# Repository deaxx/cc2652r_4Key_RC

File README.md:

# cc2652r/rb/p_4Key_RC
Box
https://aliexpress.ru/item/1005004141598897.html

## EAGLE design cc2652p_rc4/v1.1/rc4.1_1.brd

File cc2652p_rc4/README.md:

# Not recommended for assembly!

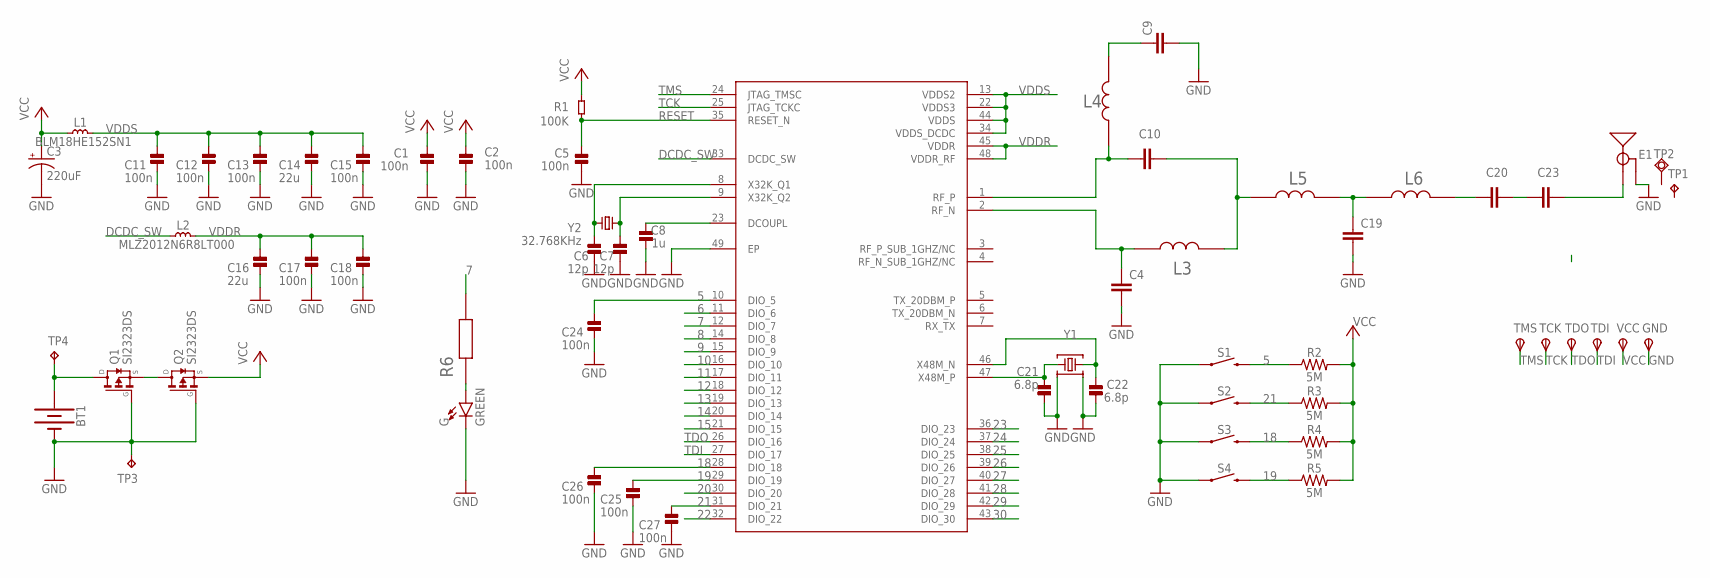
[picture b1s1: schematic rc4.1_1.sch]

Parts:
BT1: BATTERY-20MM_SMD_4LEGS_OVERPASTE; BATTCON_20MM_4LEGS_OVERPASTE
C1, C2, C5, C11, C12, C13, C15, C17, C18, C24, C25, C26, C27: 100n; _PKG_C_0402
C3: 220uF; EIA3528
C4: 1pf; CAPC1005X40N
C6, C7: 12p; _PKG_C_0402
C8: 1u; _PKG_C_0402
C9: 12pF; CAPC1005X40N
C10, C19: 1pF; CAPC1005X40N
C14, C16: 22u; _PKG_C_0805
C20: 12p; CAPC1005X40N
C21, C22: 6.8p; _PKG_C_0402
C23: 1.8pF; CAPC1005X40N
E1: ANTENNA-GROUNDEDTRACE-15.2MM; TRACE_ANTENNA_2.4GHZ_15.2MM
G: GREEN; LED-0603
GND: TPSTP11R; TP11R
IC3: CC2652R1FRGZ; RGZ0048A-IPC_B
L1: BLM18HE152SN1; _PKG_L_0603
L2: MLZ2012N6R8LT000; _PKG_C_0805
L3, L4: 2.4nH; INDC1005X40N
L5, L6: 2nH; INDC1005X40N
Q1, Q2: SI2323DS; SOT23
R1: 100K; _PKG_C_0402
R2, R3, R4, R5: 5M; 0603
R6: 2.2k; RESC1005X40N
S1, S2, S3, S4: MOMENTARY-SWITCH-SPST-SMD-5.2MM; TACTILE_SWITCH_SMD_5.2MM
TCK: TPSTP11R; TP11R
TDI: TPSTP11R; TP11R
TDO: TPSTP11R; TP11R
TMS: TPSTP11R; TP11R
TP1: TPTP06SQ; TP06SQ
TP2: TPSQTP15SQ; TP15SQ
TP3, TP4: TPB2,54; B2,54
VCC: TPSTP11R; TP11R
Y1: Q22FA12800150; XTAL-4P-2016
Y2: 32.768KHz; XTAL-2P-3215

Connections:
5: C24.1, IC3.10 (DIO_5), R2.1, S1.3 (2)
6: IC3.11 (DIO_6)
7: IC3.12 (DIO_7), R6.2
8: IC3.14 (DIO_8)
9: IC3.15 (DIO_9)
10: IC3.16 (DIO_10)
11: IC3.17 (DIO_11)
12: IC3.18 (DIO_12)
13: IC3.19 (DIO_13)
14: IC3.20 (DIO_14)
15: IC3.21 (DIO_15)
18: C26.1, IC3.28 (DIO_18), R4.1, S3.3 (2)
19: C25.1, IC3.29 (DIO_19), R5.1, S4.3 (2)
20: IC3.30 (DIO_20)
21: C27.1, IC3.31 (DIO_21), R3.1, S2.3 (2)
22: IC3.32 (DIO_22)
23: IC3.36 (DIO_23)
24: IC3.37 (DIO_24)
25: IC3.38 (DIO_25)
26: IC3.39 (DIO_26)
27: IC3.40 (DIO_27)
28: IC3.41 (DIO_28)
29: IC3.42 (DIO_29)
30: IC3.43 (DIO_30)
DCDC_SW: IC3.33 (DCDC_SW), L2.1
DCOUPL: C8.2, IC3.23 (DCOUPL)
GND: BT1.2 (-), C1.1, C2.1, C3.C (-), C4.2, C5.1, C6.1, C7.1, C8.1, C9.2, C11.2, C12.2, C13.2, C14.2, C15.2, C16.2, C17.2, C18.2, C19.2, C21.1, C22.1, C24.2, C25.2, C26.2, C27.2, E1.GND, G.C, GND.TP, IC3.49 (EP), Q1.1 (G), Q2.1 (G), S1.1, S2.1, S3.1, S4.1, TP3.TP, Y1.2, Y1.4
unnamed: C20.2, C23.1
unnamed: C20.1, L6.2
unnamed: C22.2, IC3.46 (X48M_N), Y1.3
unnamed: BT1.1 (+), Q1.3 (D), TP4.TP
unnamed: G.A, R6.1
unnamed: Q1.2 (S), Q2.3 (D)
unnamed: C10.1, IC3.1 (RF_P), L4.1
unnamed: C4.1, IC3.2 (RF_N), L3.1
unnamed: C10.2, L3.2, L5.1
unnamed: C21.2, IC3.47 (X48M_P), Y1.1
unnamed: C9.1, L4.2
unnamed: C23.2, E1.ANT (SIGNAL)
unnamed: C19.1, L5.2, L6.1
RESET: C5.2, IC3.35 (RESET_N), R1.1
TCK: IC3.25 (JTAG_TCKC), TCK.TP
TDI: IC3.27 (DIO_17), TDI.TP
TDO: IC3.26 (DIO_16), TDO.TP
TMS: IC3.24 (JTAG_TMSC), TMS.TP
VCC: C1.2, C2.2, C3.A (+), L1.1, Q2.2 (S), R1.2, R2.2, R3.2, R4.2, R5.2, VCC.TP
VDDR: C16.1, C17.1, C18.1, IC3.45 (VDDR), IC3.48 (VDDR_RF), L2.2
VDDS: C11.1, C12.1, C13.1, C14.1, C15.1, IC3.13 (VDDS2), IC3.22 (VDDS3), IC3.34 (VDDS_DCDC), IC3.44 (VDDS), L1.2
X32K_Q1: C6.2, IC3.8 (X32K_Q1), Y2.1
X32K_Q2: C7.2, IC3.9 (X32K_Q2), Y2.2

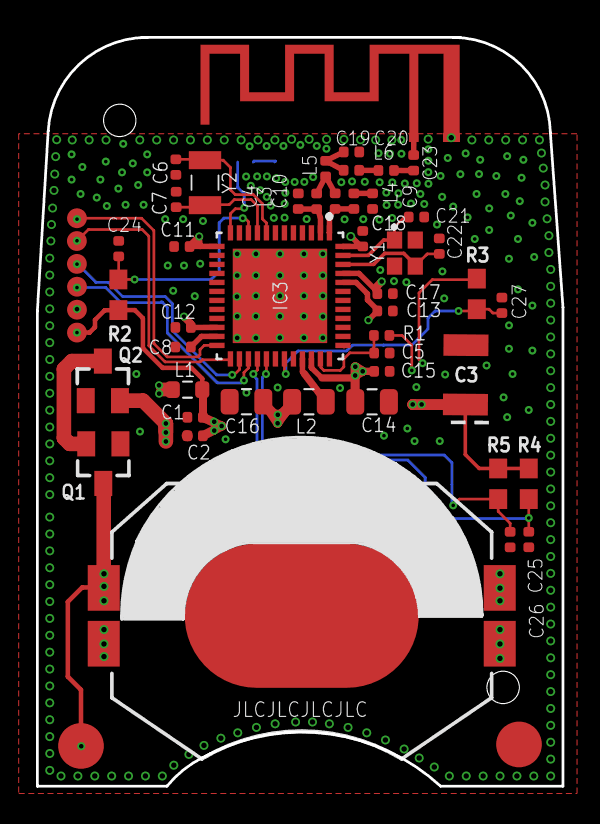
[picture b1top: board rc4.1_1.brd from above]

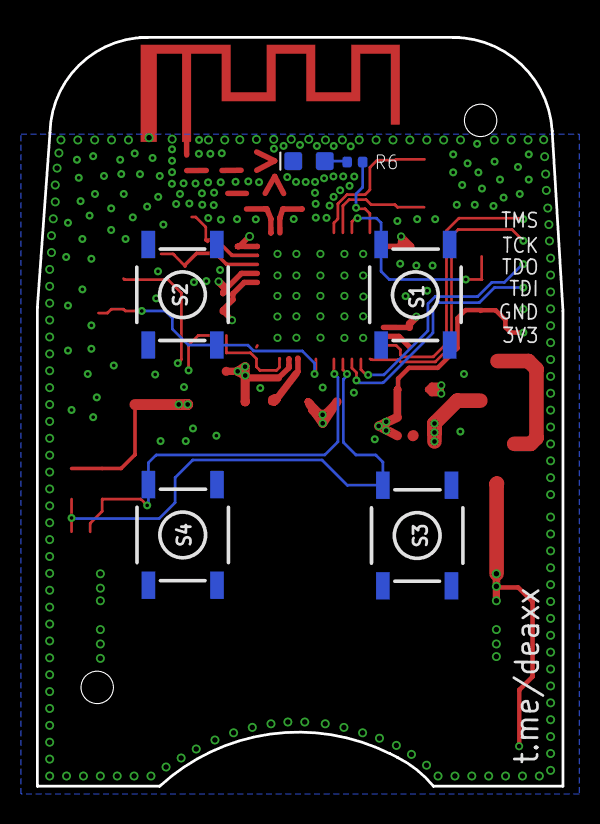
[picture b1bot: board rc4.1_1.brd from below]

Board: 4 copper layers, 29.2 x 41.6 mm, 61 parts (6 on the bottom side), 31 nets.

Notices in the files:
parts and their libraries:
SparkFun-RF2: Licensing: Creative Commons ShareAlike 4.0 International - https://creativecommons.org/licenses/by-sa/4.0
COPYRIGHT: Copyright (C) 2022 Ultra Librarian. All rights reserved.
